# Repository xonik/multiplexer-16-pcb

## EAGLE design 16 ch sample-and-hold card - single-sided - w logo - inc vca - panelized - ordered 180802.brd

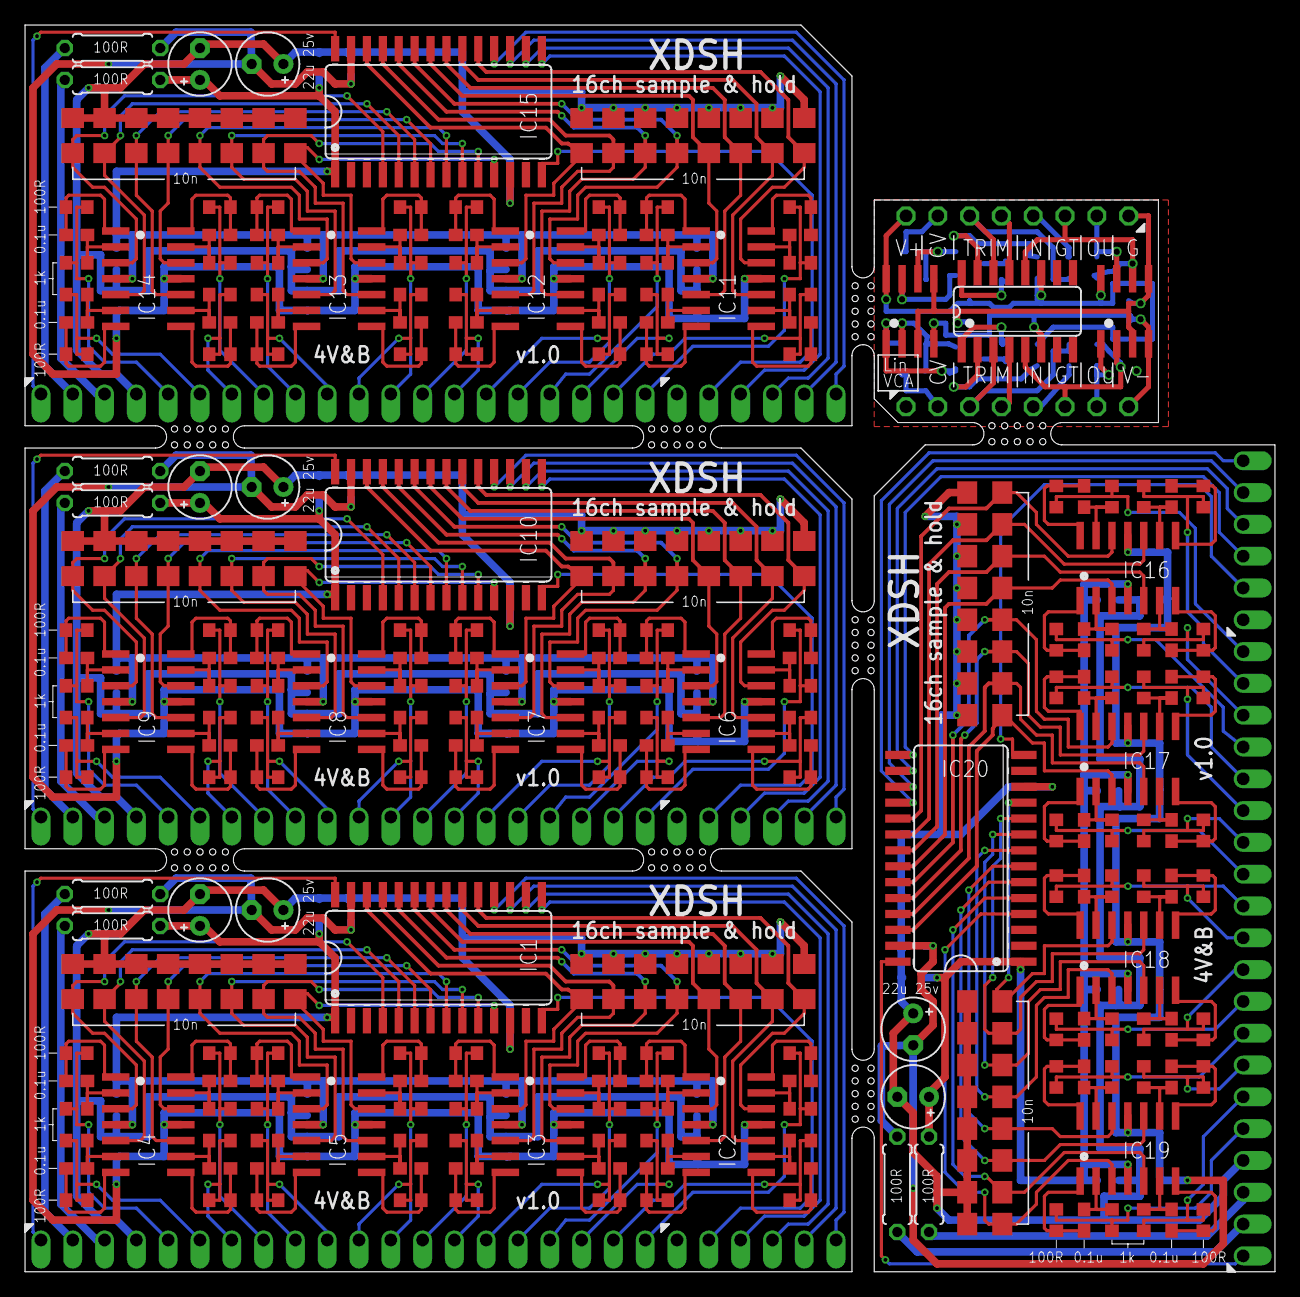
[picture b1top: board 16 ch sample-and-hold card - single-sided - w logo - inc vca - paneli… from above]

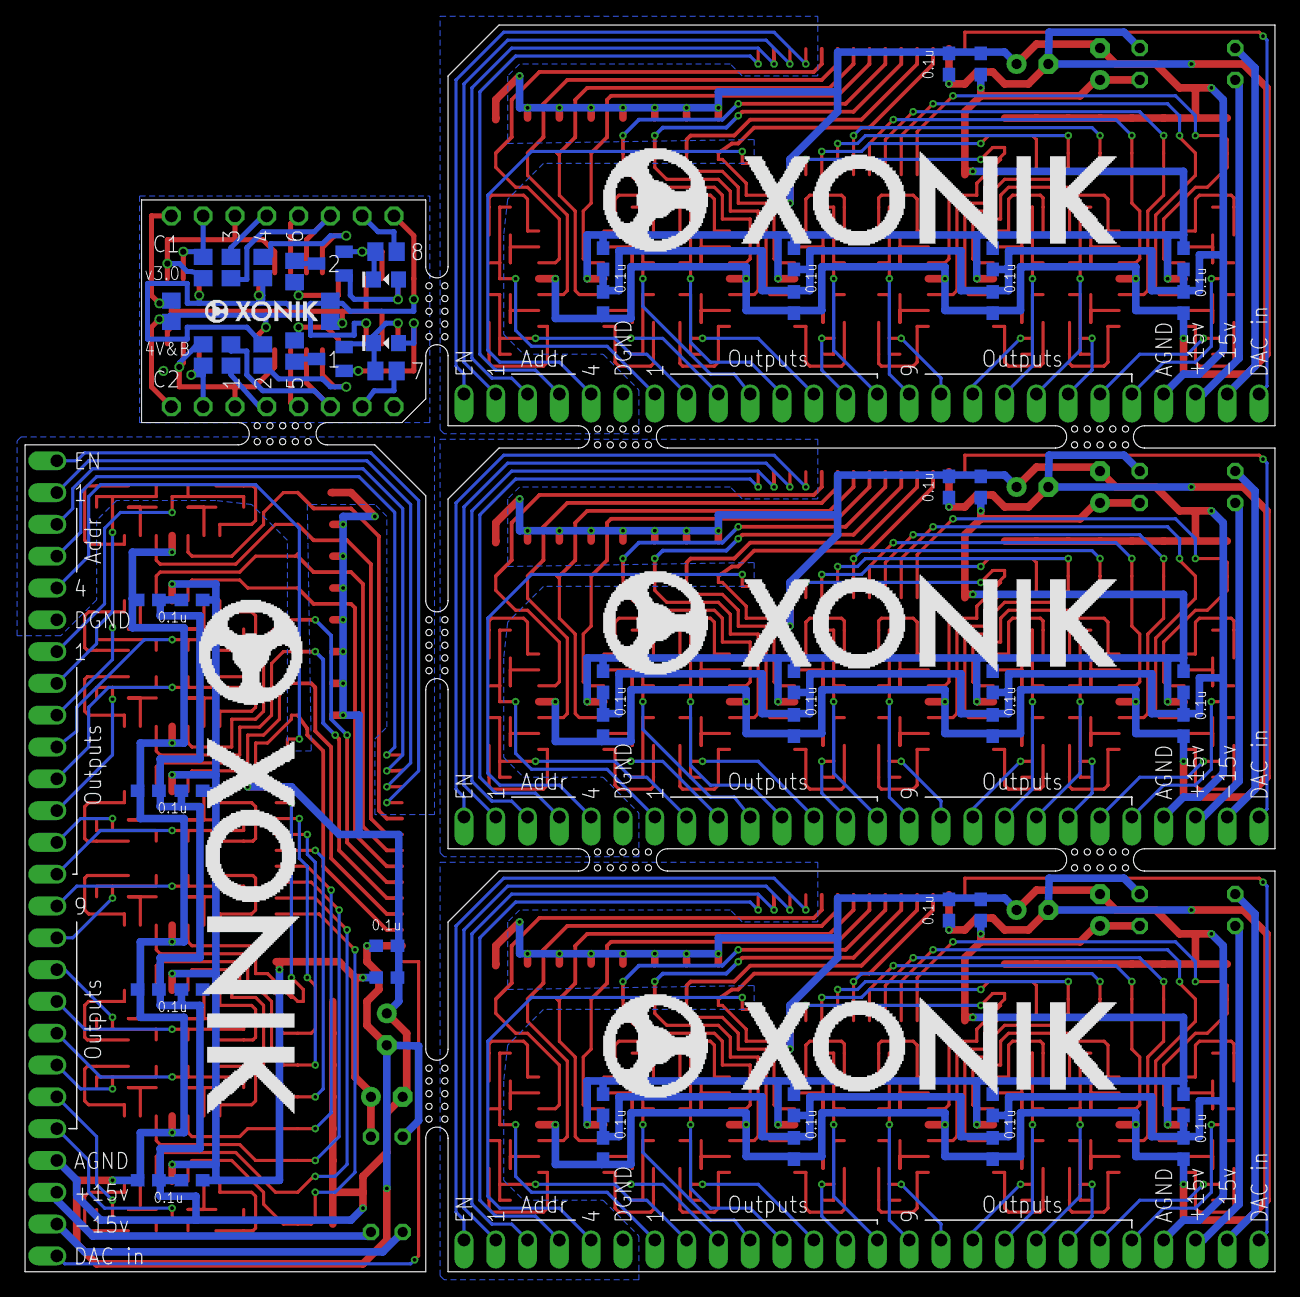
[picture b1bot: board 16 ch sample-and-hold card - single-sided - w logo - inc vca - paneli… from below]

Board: 2 copper layers, 99.8 x 99.6 mm, 361 parts (56 on the bottom side), 325 nets.

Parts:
C1, C12, C13, C14, C15, C16, C17, C18, C19, C20, C21, C30, C31, C32, C33, C34, C35, C36, C37, C38, C39, C40, C41, C42, C43, C44, C48, C49, C51, C52, C53, C58, C59, C60, C61, C62, C67, C68, C69, C70, C71, C76, C77, C78, C79, C80, C81, C84, C85, C86, C87, C88, C92, C93, C95, C96, C97, C102, C103, C104, C105, C106, C111, C112, C113, C114, C115, C120, C121, C122, C123, C124, C125, C128, C129, C130, C131, C132, C136, C137, C139, C140, C141, C146, C147, C148, C149, C150, C155, C156, C157, C158, C159, C164, C165, C166, C167, C168, C169, C172, C173, C174, C175, C176: 0.1uF; C0603
C2, C3, C82, C83, C126, C127, C170, C171: 22uF 25V; E2,5-5
C4, C5, C6, C7, C8, C9, C10, C11, C22, C23, C24, C25, C26, C27, C28, C29, C45, C46, C47, C50, C54, C55, C56, C57, C63, C64, C65, C66, C72, C73, C74, C75, C89, C90, C91, C94, C98, C99, C100, C101, C107, C108, C109, C110, C116, C117, C118, C119, C133, C134, C135, C138, C142, C143, C144, C145, C151, C152, C153, C154, C160, C161, C162, C163: 10nF; C1206
C177, C178: 47p; C0805
C179, C180: 100n; C0805
D1, D2: 1N41480805; D0805-J
IC1, IC10, IC15, IC20: MAX306CWI; SO28L
IC2, IC3, IC4, IC5, IC6, IC7, IC8, IC9, IC11, IC12, IC13, IC14, IC16, IC17, IC18, IC19: TL074D; SO14
IC21: LM13700M; SO16
IC22, IC23: TL072D; SO08
LEFT: MA08-1J
Q1, Q2: MMBT3906LT1SMD; SOT23-BEC
R1, R2, R67, R68, R101, R102, R135, R136: 100R; 0207/7
R3, R5, R7, R9, R11, R13, R15, R17, R19, R21, R23, R25, R27, R29, R31, R33, R36, R38, R40, R41, R44, R46, R48, R49, R52, R54, R56, R57, R60, R62, R64, R65, R70, R72, R74, R75, R78, R80, R82, R83, R86, R88, R90, R91, R94, R96, R98, R99, R104, R106, R108, R109, R112, R114, R116, R117, R120, R122, R124, R125, R128, R130, R132, R133: 1k; R0603
R4, R6, R8, R10, R12, R14, R16, R18, R20, R22, R24, R26, R28, R30, R32, R34, R35, R37, R39, R42, R43, R45, R47, R50, R51, R53, R55, R58, R59, R61, R63, R66, R69, R71, R73, R76, R77, R79, R81, R84, R85, R87, R89, R92, R93, R95, R97, R100, R103, R105, R107, R110, R111, R113, R115, R118, R119, R121, R123, R126, R127, R129, R131, R134: 100R; R0603
R137, R139: 27k; R0805
R138, R140: 12k; R0805
R141, R142: 88k2; R0805
R143, R144: 3k3; R0805
RIGHT: MA08-1J
SV1, SV2, SV3, SV4: SIP-PIN20-1J
U$1, U$2, U$3, U$4: MA06-1JP; SIP-PIN06-1J

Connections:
+15V: C3.+, C12.1, C13.1, C30.1, C31.1, C40.2, IC1.1, IC2.4, IC3.4, IC4.4, IC5.4, R2.1
+15V1: C53.1, C62.1, C71.1, C80.1, C83.+, C84.2, IC6.4, IC7.4, IC8.4, IC9.4, IC10.1, R67.1
+15V2: C97.1, C106.1, C115.1, C124.1, C127.+, C128.2, IC11.4, IC12.4, IC13.4, IC14.4, IC15.1, R101.1
+15V3: C141.1, C150.1, C159.1, C168.1, C171.+, C172.2, IC16.4, IC17.4, IC18.4, IC19.4, IC20.1, R135.1
-15V: C1.1, C2.-, C41.2, C42.2, C43.2, C44.2, IC1.27, IC2.11, IC3.11, IC4.11, IC5.11, R1.1
-15V1: C81.1, C82.-, C85.2, C86.2, C87.2, C88.2, IC6.11, IC7.11, IC8.11, IC9.11, IC10.27, R68.1
-15V2: C125.1, C126.-, C129.2, C130.2, C131.2, C132.2, IC11.11, IC12.11, IC13.11, IC14.11, IC15.27, R102.1
-15V3: C169.1, C170.-, C173.2, C174.2, C175.2, C176.2, IC16.11, IC17.11, IC18.11, IC19.11, IC20.27, R136.1
A0: IC1.17, U$1.5
A1: IC1.16, U$1.4
A2: IC1.15, U$1.3
A3: IC1.14, U$1.2
A4: IC10.14, U$2.2
A5: IC10.17, U$2.5
A6: IC10.16, U$2.4
A7: IC10.15, U$2.3
A8: IC15.14, U$3.2
A9: IC15.17, U$3.5
A10: IC15.16, U$3.4
A11: IC15.15, U$3.3
A12: IC20.14, U$4.2
A13: IC20.17, U$4.5
A14: IC20.16, U$4.4
A15: IC20.15, U$4.3
AGND: C1.2, C2.+, C3.-, C4.1, C5.1, C6.1, C7.1, C8.1, C9.1, C10.1, C11.1, C12.2, C13.2, C22.1, C23.1, C24.1, C25.1, C26.1, C27.1, C28.1, C29.1, C30.2, C31.2, C40.1, C41.1, C42.1, C43.1, C44.1, IC1.12, SV1.4
AGND1: C45.1, C46.1, C47.1, C50.1, C53.2, C54.1, C55.1, C56.1, C57.1, C62.2, C63.1, C64.1, C65.1, C66.1, C71.2, C72.1, C73.1, C74.1, C75.1, C80.2, C81.2, C82.+, C83.-, C84.1, C85.1, C86.1, C87.1, C88.1, IC10.12, SV2.4
AGND2: C89.1, C90.1, C91.1, C94.1, C97.2, C98.1, C99.1, C100.1, C101.1, C106.2, C107.1, C108.1, C109.1, C110.1, C115.2, C116.1, C117.1, C118.1, C119.1, C124.2, C125.2, C126.+, C127.-, C128.1, C129.1, C130.1, C131.1, C132.1, IC15.12, SV3.4
AGND3: C133.1, C134.1, C135.1, C138.1, C141.2, C142.1, C143.1, C144.1, C145.1, C150.2, C151.1, C152.1, C153.1, C154.1, C159.2, C160.1, C161.1, C162.1, C163.1, C168.2, C169.2, C170.+, C171.-, C172.1, C173.1, C174.1, C175.1, C176.1, IC20.12, SV4.4
CV1: LEFT.2, R143.2
CV2: R144.2, RIGHT.7
DAC: IC1.28, SV1.1
DAC1: IC10.28, SV2.1
DAC2: IC15.28, SV3.1
DAC3: IC20.28, SV4.1
EN: IC1.18, U$1.6
EN1: IC10.18, U$2.6
EN2: IC15.18, U$3.6
EN3: IC20.18, U$4.6
GAIN_TRIM1: C178.1, IC21.5, IC23.2, LEFT.6
GAIN_TRIM2: C177.1, IC21.12, IC23.6, RIGHT.3
GND: C179.1, C180.2, IC22.3, IC22.5, IC23.3, IC23.5, RIGHT.1
IN1: C4.2, IC1.19, IC2.12
IN2: C50.2, IC6.12, IC10.19
IN3: C5.2, IC1.20, IC2.10
IN4: C6.2, IC1.21, IC2.5
IN5: C47.2, IC6.10, IC10.20
IN6: C7.2, IC1.22, IC2.3
IN7: C46.2, IC6.5, IC10.21
IN8: C45.2, IC6.3, IC10.22
IN9: C8.2, IC1.23, IC3.12
IN10: C57.2, IC7.12, IC10.23
IN11: C9.2, IC1.24, IC3.10
IN12: C10.2, IC1.25, IC3.5
IN13: C56.2, IC7.10, IC10.24
IN14: C11.2, IC1.26, IC3.3
IN15: C55.2, IC7.5, IC10.25
IN16: C54.2, IC7.3, IC10.26
IN17: C26.2, IC1.11, IC5.12
IN18: C63.2, IC8.3, IC10.8
IN19: C27.2, IC1.10, IC5.10
IN20: C28.2, IC1.9, IC5.5
IN21: C64.2, IC8.5, IC10.9
IN22: C29.2, IC1.8, IC5.3
IN23: C65.2, IC8.10, IC10.10
IN24: C66.2, IC8.12, IC10.11
IN25: C22.2, IC1.7, IC4.12
IN26: C72.2, IC9.3, IC10.4
IN27: C23.2, IC1.6, IC4.10
IN28: C24.2, IC1.5, IC4.5
IN29: C73.2, IC9.5, IC10.5
IN30: C25.2, IC1.4, IC4.3
IN31: C74.2, IC9.10, IC10.6
IN32: C75.2, IC9.12, IC10.7
IN33: C94.2, IC11.12, IC15.19
IN34: C91.2, IC11.10, IC15.20
IN35: C90.2, IC11.5, IC15.21
IN36: C89.2, IC11.3, IC15.22
IN37: C101.2, IC12.12, IC15.23
IN38: C100.2, IC12.10, IC15.24
IN39: C99.2, IC12.5, IC15.25
IN40: C98.2, IC12.3, IC15.26
IN41: C107.2, IC13.3, IC15.8
IN42: C108.2, IC13.5, IC15.9
IN43: C109.2, IC13.10, IC15.10
IN44: C110.2, IC13.12, IC15.11
IN45: C116.2, IC14.3, IC15.4
IN46: C117.2, IC14.5, IC15.5
IN47: C118.2, IC14.10, IC15.6
IN48: C119.2, IC14.12, IC15.7
IN49: C138.2, IC16.12, IC20.19
IN50: C135.2, IC16.10, IC20.20
IN51: C134.2, IC16.5, IC20.21
IN52: C133.2, IC16.3, IC20.22
IN53: C145.2, IC17.12, IC20.23
IN54: C144.2, IC17.10, IC20.24
IN55: C143.2, IC17.5, IC20.25
IN56: C142.2, IC17.3, IC20.26
IN57: C151.2, IC18.3, IC20.8
IN58: C152.2, IC18.5, IC20.9
IN59: C153.2, IC18.10, IC20.10
IN60: C154.2, IC18.12, IC20.11
IN61: C160.2, IC19.3, IC20.4
IN62: C161.2, IC19.5, IC20.5
IN63: C162.2, IC19.10, IC20.6
IN64: C163.2, IC19.12, IC20.7
IN65: LEFT.5, R137.1
IN66: R139.1, RIGHT.4
unnamed: C17.2, IC2.2, R9.1
unnamed: C17.1, IC2.1, R10.1
unnamed: C16.1, IC2.7, R8.1
unnamed: C15.1, IC2.8, R6.1
unnamed: C16.2, IC2.6, R7.1
unnamed: C14.1, IC2.14, R4.1
unnamed: C15.2, IC2.9, R5.1
unnamed: C14.2, IC2.13, R3.1
unnamed: C21.1, IC3.1, R18.1
unnamed: C21.2, IC3.2, R17.1
unnamed: C48.1, IC6.1, R35.1
unnamed: C48.2, IC6.2, R36.1
unnamed: C49.1, IC6.7, R37.1
unnamed: C49.2, IC6.6, R38.1
unnamed: C51.1, IC6.8, R39.1
unnamed: C52.1, IC6.14, R42.1
unnamed: C51.2, IC6.9, R40.1
unnamed: C52.2, IC6.13, R41.1
unnamed: C20.1, IC3.7, R16.1
unnamed: C20.2, IC3.6, R15.1
unnamed: C19.1, IC3.8, R14.1
unnamed: C18.1, IC3.14, R12.1
unnamed: C19.2, IC3.9, R13.1
unnamed: C18.2, IC3.13, R11.1
unnamed: C58.1, IC7.1, R43.1
unnamed: C58.2, IC7.2, R44.1
unnamed: C59.1, IC7.7, R45.1
unnamed: C59.2, IC7.6, R46.1
unnamed: C60.1, IC7.8, R47.1
unnamed: C61.1, IC7.14, R50.1
unnamed: C60.2, IC7.9, R48.1
unnamed: C61.2, IC7.13, R49.1
unnamed: C39.1, IC5.1, R34.1
unnamed: C39.2, IC5.2, R33.1
unnamed: C38.1, IC5.7, R32.1
unnamed: C38.2, IC5.6, R31.1
unnamed: C37.1, IC5.8, R30.1
unnamed: C36.1, IC5.14, R28.1
unnamed: C37.2, IC5.9, R29.1
unnamed: C36.2, IC5.13, R27.1
unnamed: C67.1, IC8.1, R51.1
unnamed: C67.2, IC8.2, R52.1
unnamed: C68.1, IC8.7, R53.1
unnamed: C68.2, IC8.6, R54.1
unnamed: C69.1, IC8.8, R55.1
unnamed: C70.1, IC8.14, R58.1
unnamed: C69.2, IC8.9, R56.1
unnamed: C70.2, IC8.13, R57.1
unnamed: C35.1, IC4.1, R26.1
unnamed: C35.2, IC4.2, R25.1
unnamed: C34.1, IC4.7, R24.1
unnamed: C34.2, IC4.6, R23.1
unnamed: C33.1, IC4.8, R22.1
unnamed: C32.1, IC4.14, R20.1
unnamed: C33.2, IC4.9, R21.1
unnamed: C32.2, IC4.13, R19.1
unnamed: C76.1, IC9.1, R59.1
unnamed: C76.2, IC9.2, R60.1
unnamed: C77.1, IC9.7, R61.1
unnamed: C77.2, IC9.6, R62.1
unnamed: C78.1, IC9.8, R63.1
unnamed: C79.1, IC9.14, R66.1
unnamed: C78.2, IC9.9, R64.1
unnamed: C79.2, IC9.13, R65.1
unnamed: C92.1, IC11.1, R69.1
unnamed: C92.2, IC11.2, R70.1
unnamed: C93.1, IC11.7, R71.1
unnamed: C93.2, IC11.6, R72.1
unnamed: C95.1, IC11.8, R73.1
unnamed: C96.1, IC11.14, R76.1
unnamed: C95.2, IC11.9, R74.1
unnamed: C96.2, IC11.13, R75.1
unnamed: C102.1, IC12.1, R77.1
unnamed: C102.2, IC12.2, R78.1
unnamed: C103.1, IC12.7, R79.1
unnamed: C103.2, IC12.6, R80.1
unnamed: C104.1, IC12.8, R81.1
unnamed: C105.1, IC12.14, R84.1
unnamed: C104.2, IC12.9, R82.1
unnamed: C105.2, IC12.13, R83.1
unnamed: C111.1, IC13.1, R85.1
unnamed: C111.2, IC13.2, R86.1
unnamed: C112.1, IC13.7, R87.1
unnamed: C112.2, IC13.6, R88.1
unnamed: C113.1, IC13.8, R89.1
unnamed: C114.1, IC13.14, R92.1
unnamed: C113.2, IC13.9, R90.1
unnamed: C114.2, IC13.13, R91.1
unnamed: C120.1, IC14.1, R93.1
unnamed: C120.2, IC14.2, R94.1
unnamed: C121.1, IC14.7, R95.1
unnamed: C121.2, IC14.6, R96.1
unnamed: C122.1, IC14.8, R97.1
unnamed: C123.1, IC14.14, R100.1
unnamed: C122.2, IC14.9, R98.1
unnamed: C123.2, IC14.13, R99.1
unnamed: C136.1, IC16.1, R103.1
unnamed: C136.2, IC16.2, R104.1
unnamed: C137.1, IC16.7, R105.1
unnamed: C137.2, IC16.6, R106.1
unnamed: C139.1, IC16.8, R107.1
unnamed: C140.1, IC16.14, R110.1
unnamed: C139.2, IC16.9, R108.1
unnamed: C140.2, IC16.13, R109.1
unnamed: C146.1, IC17.1, R111.1
unnamed: C146.2, IC17.2, R112.1
unnamed: C147.1, IC17.7, R113.1
unnamed: C147.2, IC17.6, R114.1
unnamed: C148.1, IC17.8, R115.1
unnamed: C149.1, IC17.14, R118.1
unnamed: C148.2, IC17.9, R116.1
unnamed: C149.2, IC17.13, R117.1
unnamed: C155.1, IC18.1, R119.1
unnamed: C155.2, IC18.2, R120.1
unnamed: C156.1, IC18.7, R121.1
unnamed: C156.2, IC18.6, R122.1
unnamed: C157.1, IC18.8, R123.1
unnamed: C158.1, IC18.14, R126.1
unnamed: C157.2, IC18.9, R124.1
unnamed: C158.2, IC18.13, R125.1
unnamed: C164.1, IC19.1, R127.1
unnamed: C164.2, IC19.2, R128.1
unnamed: C165.1, IC19.7, R129.1
unnamed: C165.2, IC19.6, R130.1
unnamed: C166.1, IC19.8, R131.1
unnamed: C167.1, IC19.14, R134.1
unnamed: C166.2, IC19.9, R132.1
unnamed: C167.2, IC19.13, R133.1
unnamed: Q1.C, R141.1
unnamed: Q2.C, R142.1
unnamed: D1.C, IC22.2, Q1.E, R143.1
unnamed: IC21.1, R141.2
unnamed: IC21.2, R138.2
unnamed: IC21.16, R142.2
unnamed: D2.C, IC22.6, Q2.E, R144.1
unnamed: IC21.15, R140.2
unnamed: D2.A, IC22.7, Q2.B
unnamed: D1.A, IC22.1, Q1.B
OUT0: R3.2, R4.2, SV1.20
OUT1: R5.2, R6.2, SV1.19
OUT2: R41.2, R42.2, SV2.20
OUT3: R37.2, R38.2, SV2.18
OUT4: R35.2, R36.2, SV2.17
OUT5: R39.2, R40.2, SV2.19
OUT6: R7.2, R8.2, SV1.18
OUT7: R9.2, R10.2, SV1.17
OUT8: R11.2, R12.2, SV1.16
OUT9: R13.2, R14.2, SV1.15
OUT10: R43.2, R44.2, SV2.13
OUT11: R45.2, R46.2, SV2.14
OUT12: R47.2, R48.2, SV2.15
OUT13: R49.2, R50.2, SV2.16
OUT14: R15.2, R16.2, SV1.14
OUT15: R17.2, R18.2, SV1.13
OUT16: R27.2, R28.2, SV1.12
OUT17: R29.2, R30.2, SV1.11
OUT18: R51.2, R52.2, SV2.9
OUT19: R53.2, R54.2, SV2.10
OUT20: R55.2, R56.2, SV2.11
OUT21: R57.2, R58.2, SV2.12
OUT22: R31.2, R32.2, SV1.10
OUT23: R33.2, R34.2, SV1.9
OUT24: R19.2, R20.2, SV1.8
OUT25: R21.2, R22.2, SV1.7
OUT26: R59.2, R60.2, SV2.5
OUT27: R61.2, R62.2, SV2.6
OUT28: R63.2, R64.2, SV2.7
OUT29: R65.2, R66.2, SV2.8
OUT30: R23.2, R24.2, SV1.6
OUT31: R25.2, R26.2, SV1.5
OUT32: R75.2, R76.2, SV3.20
OUT33: R71.2, R72.2, SV3.18
OUT34: R69.2, R70.2, SV3.17
OUT35: R73.2, R74.2, SV3.19
OUT36: R77.2, R78.2, SV3.13
OUT37: R79.2, R80.2, SV3.14
OUT38: R81.2, R82.2, SV3.15
OUT39: R83.2, R84.2, SV3.16
OUT40: R85.2, R86.2, SV3.9
OUT41: R87.2, R88.2, SV3.10
OUT42: R89.2, R90.2, SV3.11
OUT43: R91.2, R92.2, SV3.12
OUT44: R93.2, R94.2, SV3.5
OUT45: R95.2, R96.2, SV3.6
OUT46: R97.2, R98.2, SV3.7
OUT47: R99.2, R100.2, SV3.8
OUT48: R109.2, R110.2, SV4.20
OUT49: R105.2, R106.2, SV4.18
OUT50: R103.2, R104.2, SV4.17
OUT51: R107.2, R108.2, SV4.19
OUT52: R111.2, R112.2, SV4.13
OUT53: R113.2, R114.2, SV4.14
OUT54: R115.2, R116.2, SV4.15
OUT55: R117.2, R118.2, SV4.16
OUT56: R119.2, R120.2, SV4.9
OUT57: R121.2, R122.2, SV4.10
OUT58: R123.2, R124.2, SV4.11
OUT59: R125.2, R126.2, SV4.12
OUT60: R127.2, R128.2, SV4.5
OUT61: R129.2, R130.2, SV4.6
OUT62: R131.2, R132.2, SV4.7
OUT63: R133.2, R134.2, SV4.8
OUT64: C178.2, IC23.1, LEFT.7
OUT65: C177.2, IC23.7, RIGHT.2
TRIM1+: IC21.3, LEFT.3, R137.2
TRIM1-: IC21.4, LEFT.4
TRIM2+: IC21.14, R139.2, RIGHT.6
TRIM2-: IC21.13, RIGHT.5
V+: R2.2, SV1.3
V+1: R67.2, SV2.3
V+2: R101.2, SV3.3
V+3: R135.2, SV4.3
V+4: C179.2, IC21.11, IC22.8, IC23.8, R138.1, R140.1, RIGHT.8
V-: R1.2, SV1.2
V-1: R68.2, SV2.2
V-2: R102.2, SV3.2
V-3: R136.2, SV4.2
V-4: C180.1, IC21.6, IC22.4, IC23.4, LEFT.8

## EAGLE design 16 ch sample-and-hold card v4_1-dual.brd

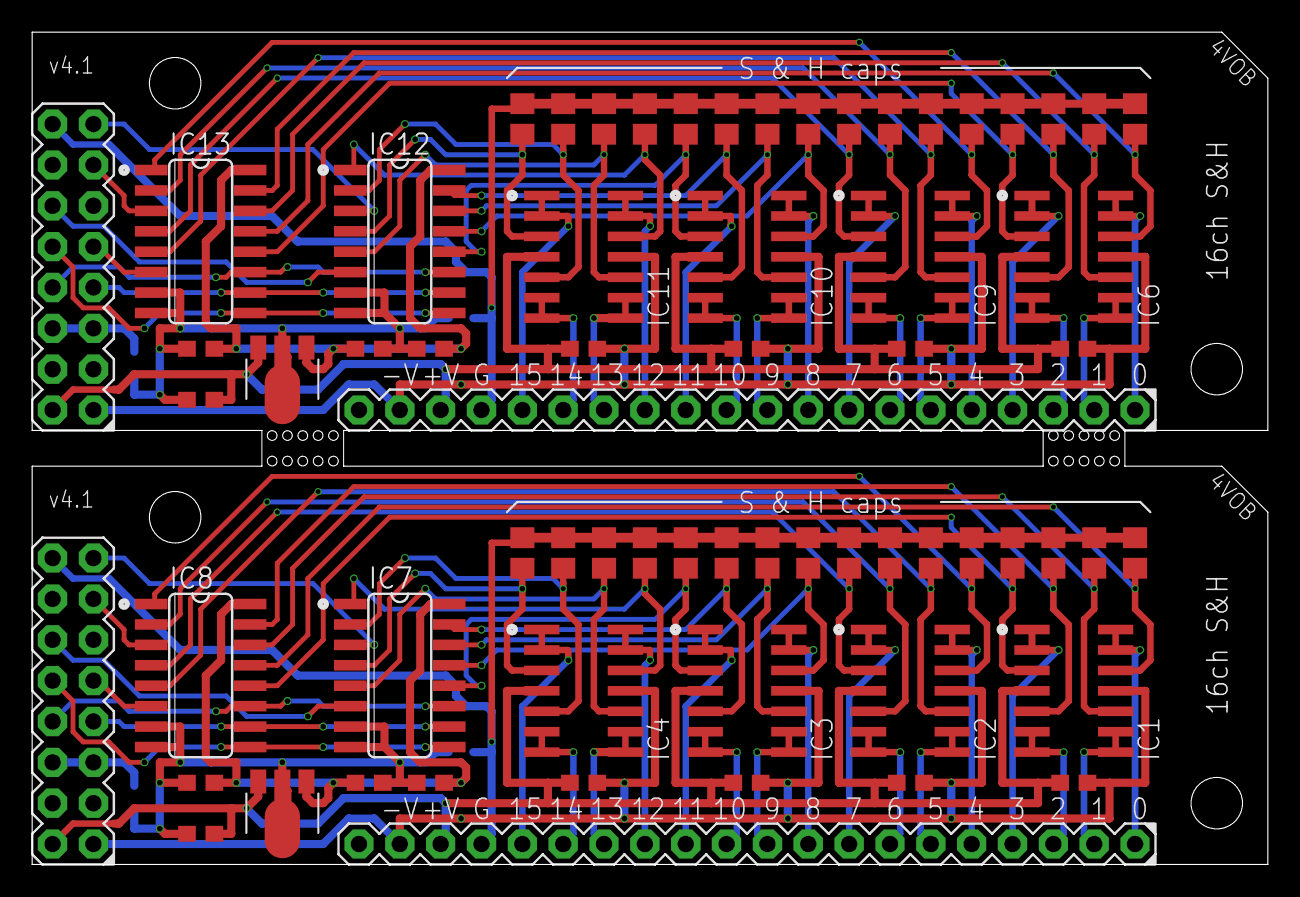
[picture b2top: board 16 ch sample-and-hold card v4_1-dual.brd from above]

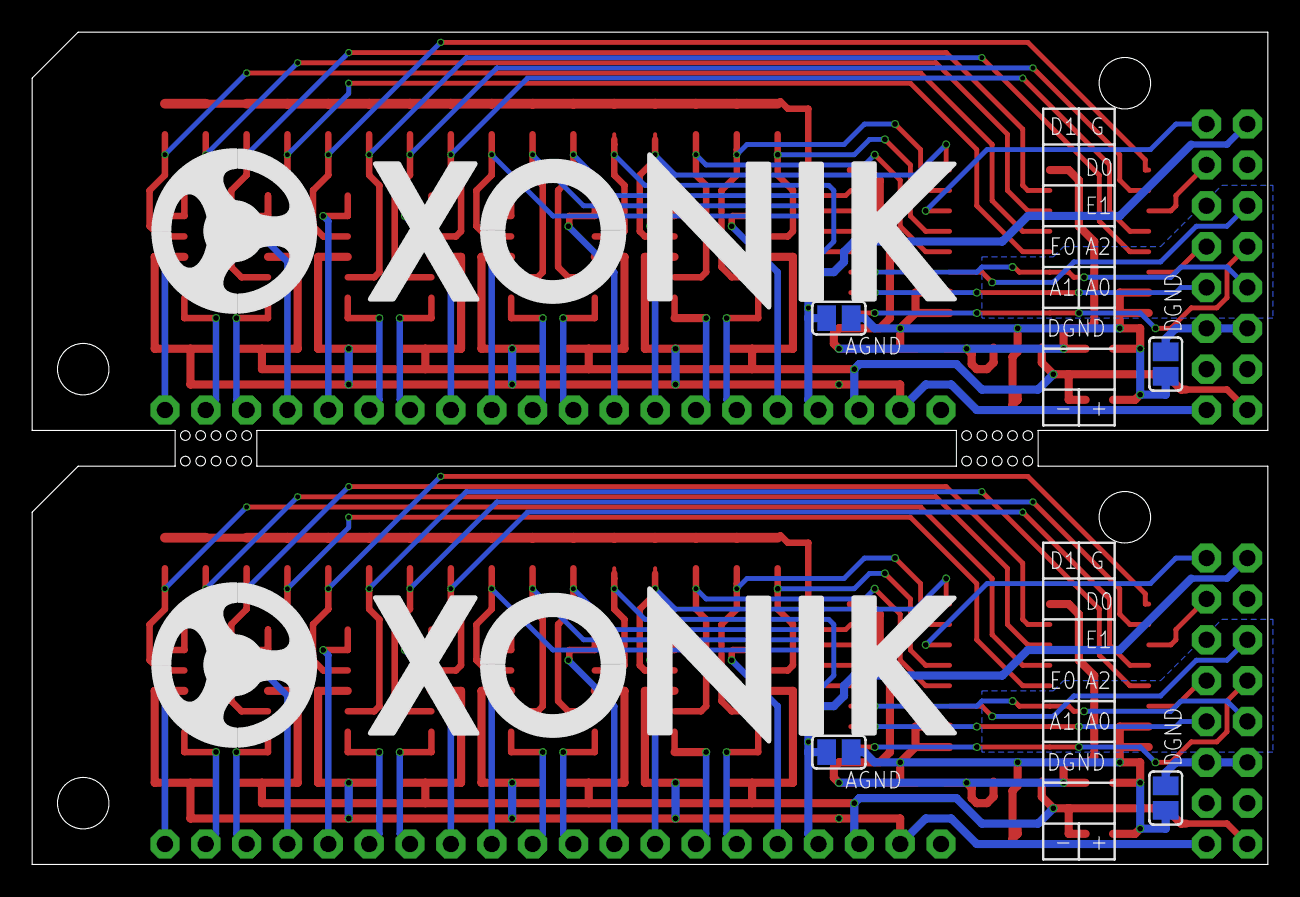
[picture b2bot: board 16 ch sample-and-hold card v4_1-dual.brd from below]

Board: 2 copper layers, 76.8 x 51.8 mm, 72 parts (6 on the bottom side), 90 nets.

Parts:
C1, C2, C12, C13, C18, C30, C31, C33, C38, C40, C44, C45, C46, C47: 0.1uF; C0603
C3, C48: 0.33uF; C0603
C4, C5, C6, C7, C8, C9, C10, C11, C14, C15, C16, C17, C19, C20, C21, C22, C23, C24, C25, C26, C27, C28, C29, C32, C34, C35, C36, C37, C39, C41, C42, C43: 10nF; C0805
IC1, IC2, IC3, IC4, IC6, IC9, IC10, IC11: TL074D; SO14
IC5, IC14: 78L05F; SOT89
IC7, IC8, IC12, IC13: 4051D; SO16
SJ1, SJ2, SJ3, SJ4: SJ
SV1, SV2: MA20-1
SV3, SV4: MA08-2J
U$1, U$2: XONIK_LOGO_50

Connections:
+5V: C1.2, C2.2, C40.2, IC5.1, IC7.16, IC8.16
+5V1: C45.2, C46.2, C47.2, IC12.16, IC13.16, IC14.1
+15V: C3.2, C12.1, C13.1, C30.1, C31.1, IC1.4, IC2.4, IC3.4, IC4.4, IC5.3, SV2.18, SV3.2
+15V1: C18.1, C33.1, C38.1, C44.1, C48.2, IC6.4, IC9.4, IC10.4, IC11.4, IC14.3, SV1.18, SV4.2
-15V: C12.2, C13.2, C30.2, C31.2, IC1.11, IC2.11, IC3.11, IC4.11, SV2.19, SV3.1
-15V1: C18.2, C33.2, C38.2, C44.2, IC6.11, IC9.11, IC10.11, IC11.11, SV1.19, SV4.1
A0: IC7.11, IC8.11, SV3.8
A1: IC7.10, IC8.10, SV3.7
A2: IC7.9, IC8.9, SV3.10
A3: IC12.11, IC13.11, SV4.8
A4: IC12.10, IC13.10, SV4.7
A5: IC12.9, IC13.9, SV4.10
AGND: C4.1, C5.1, C6.1, C7.1, C8.1, C9.1, C10.1, C11.1, C22.1, C23.1, C24.1, C25.1, C26.1, C27.1, C28.1, C29.1, SJ1.2, SV2.17, SV3.16
AGND1: C14.1, C15.1, C16.1, C17.1, C19.1, C20.1, C21.1, C32.1, C34.1, C35.1, C36.1, C37.1, C39.1, C41.1, C42.1, C43.1, SJ3.2, SV1.17, SV4.16
DAC0: IC8.3, SV3.13
DAC1: IC7.3, SV3.15
DAC2: IC12.3, SV4.15
DAC3: IC13.3, SV4.13
DGND: SJ2.1, SV3.5, SV3.6
DGND1: SJ4.1, SV4.5, SV4.6
EN0: IC8.6, SV3.9
EN1: IC7.6, SV3.12
EN2: IC13.6, SV4.9
EN3: IC12.6, SV4.12
IN_0: C4.2, IC1.12, IC8.13
IN_1: C5.2, IC1.10, IC8.14
IN_2: C6.2, IC1.5, IC8.15
IN_3: C7.2, IC1.3, IC8.12
IN_4: C8.2, IC2.12, IC8.1
IN_5: C9.2, IC2.10, IC8.5
IN_6: C10.2, IC2.5, IC8.2
IN_7: C11.2, IC2.3, IC8.4
IN_8: C26.2, IC3.12, IC7.13
IN_9: C27.2, IC3.10, IC7.14
IN_10: C28.2, IC3.5, IC7.15
IN_11: C29.2, IC3.3, IC7.12
IN_12: C22.2, IC4.12, IC7.1
IN_13: C23.2, IC4.10, IC7.5
IN_14: C24.2, IC4.5, IC7.2
IN_15: C25.2, IC4.3, IC7.4
IN_16: C17.2, IC6.12, IC13.13
IN_17: C16.2, IC6.10, IC13.14
IN_18: C15.2, IC6.5, IC13.15
IN_19: C14.2, IC6.3, IC13.12
IN_20: C32.2, IC9.12, IC13.1
IN_21: C21.2, IC9.10, IC13.5
IN_22: C20.2, IC9.5, IC13.2
IN_23: C19.2, IC9.3, IC13.4
IN_24: C34.2, IC10.3, IC12.12
IN_25: C35.2, IC10.5, IC12.15
IN_26: C36.2, IC10.10, IC12.14
IN_27: C37.2, IC10.12, IC12.13
IN_28: C39.2, IC11.3, IC12.4
IN_29: C41.2, IC11.5, IC12.2
IN_30: C42.2, IC11.10, IC12.5
IN_31: C43.2, IC11.12, IC12.1
unnamed: C45.1, C46.1, C47.1, C48.1, IC12.7, IC12.8, IC13.7, IC13.8, IC14.2, IC14.2@1, SJ3.1, SJ4.2
unnamed: C1.1, C2.1, C3.1, C40.1, IC5.2, IC5.2@1, IC7.7, IC7.8, IC8.7, IC8.8, SJ1.1, SJ2.2
OUT_0: IC1.13, IC1.14, SV2.1
OUT_1: IC1.8, IC1.9, SV2.2
OUT_2: IC1.6, IC1.7, SV2.3
OUT_3: IC1.1, IC1.2, SV2.4
OUT_4: IC2.13, IC2.14, SV2.5
OUT_5: IC2.8, IC2.9, SV2.6
OUT_6: IC2.6, IC2.7, SV2.7
OUT_7: IC2.1, IC2.2, SV2.8
OUT_8: IC3.13, IC3.14, SV2.9
OUT_9: IC3.8, IC3.9, SV2.10
OUT_10: IC3.6, IC3.7, SV2.11
OUT_11: IC3.1, IC3.2, SV2.12
OUT_12: IC4.13, IC4.14, SV2.13
OUT_13: IC4.8, IC4.9, SV2.14
OUT_14: IC4.6, IC4.7, SV2.15
OUT_15: IC4.1, IC4.2, SV2.16
OUT_16: IC6.13, IC6.14, SV1.1
OUT_17: IC6.6, IC6.7, SV1.3
OUT_18: IC6.1, IC6.2, SV1.4
OUT_19: IC6.8, IC6.9, SV1.2
OUT_20: IC9.1, IC9.2, SV1.8
OUT_21: IC9.6, IC9.7, SV1.7
OUT_22: IC9.8, IC9.9, SV1.6
OUT_23: IC9.13, IC9.14, SV1.5
OUT_24: IC10.1, IC10.2, SV1.12
OUT_25: IC10.6, IC10.7, SV1.11
OUT_26: IC10.8, IC10.9, SV1.10
OUT_27: IC10.13, IC10.14, SV1.9
OUT_28: IC11.6, IC11.7, SV1.15
OUT_29: IC11.8, IC11.9, SV1.14
OUT_30: IC11.13, IC11.14, SV1.13
OUT_31: IC11.1, IC11.2, SV1.16

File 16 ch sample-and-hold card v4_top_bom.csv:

Comment,Designator,Footprint,LCSC Part #
0.1uF,C1 C2 C12 C13 C30 C31 C40,C0603,
0.33uF,C3,C0603,
10nF,C4 C5 C6 C7 C8 C9 C10 C11 C22 C23 C24 C25 C26 C27 C28 C29,C1206,
78L05F,IC5,SOT89,
4051D,IC7 IC8,SO16,

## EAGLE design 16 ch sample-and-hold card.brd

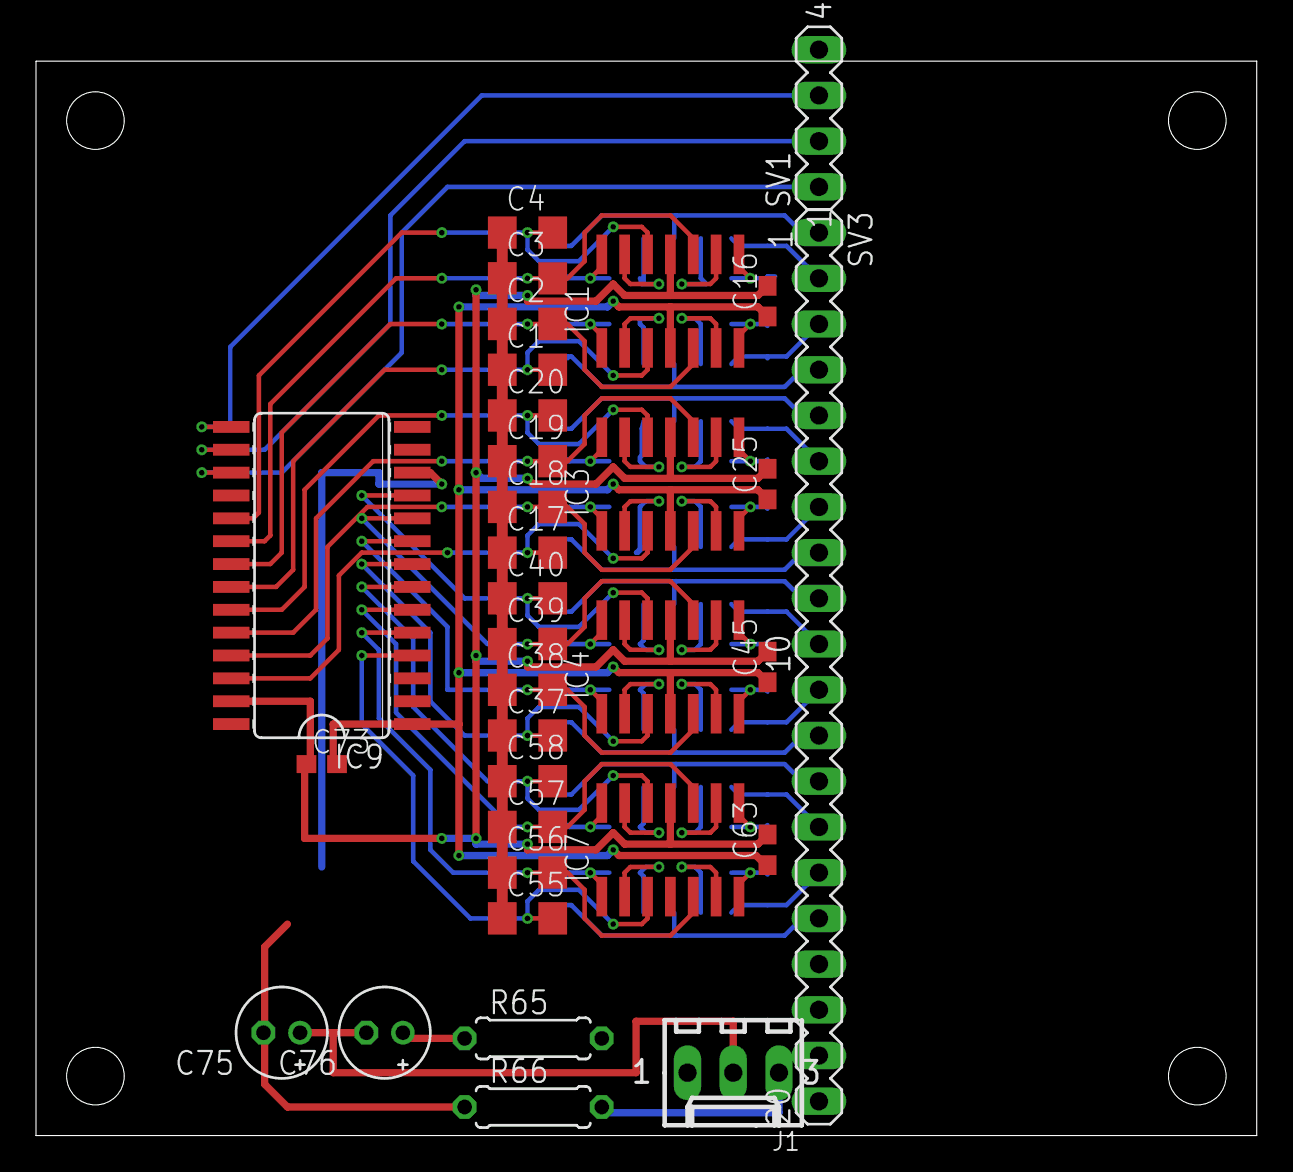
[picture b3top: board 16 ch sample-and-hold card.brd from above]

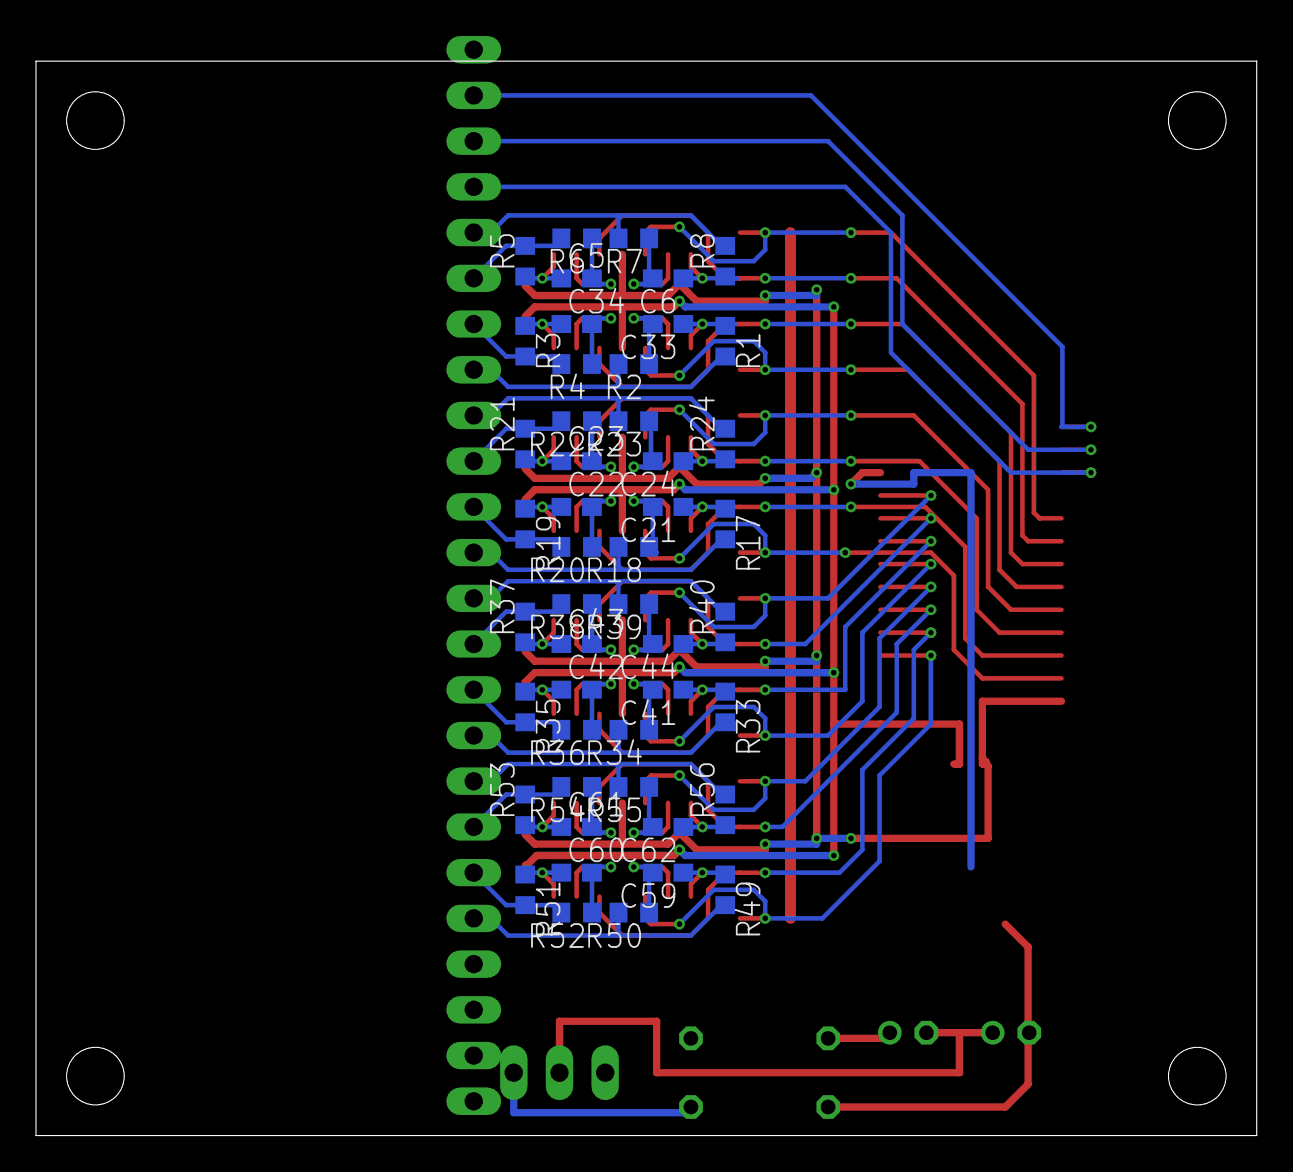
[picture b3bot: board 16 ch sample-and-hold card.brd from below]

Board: 2 copper layers, 67.8 x 59.7 mm, 81 parts (48 on the bottom side), 74 nets.

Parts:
C1, C2, C3, C4, C17, C18, C19, C20, C37, C38, C39, C40, C55, C56, C57, C58: C1206
C5, C6, C16, C21, C22, C23, C24, C25, C33, C34, C41, C42, C43, C44, C45, C59, C60, C61, C62, C63, C73: 0.1uF; C0603
C75, C76: 22uF 25V; E2-5
IC1, IC3, IC4, IC7: TL074D; SO14
IC9: MAX306CWI; SO28L
J1: 22-27-2031-03; 6410-03
R1, R3, R5, R8, R17, R19, R21, R24, R33, R35, R37, R40, R49, R51, R53, R56: 100R; R0603
R2, R4, R6, R7, R18, R20, R22, R23, R34, R36, R38, R39, R50, R52, R54, R55: 1k; R0603
R65, R66: 100; 0207/7
SV1: MA04-1
SV3: MA20-1

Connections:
+15V: C16.1, C25.1, C45.1, C63.1, C73.2, C76.+, IC1.4, IC3.4, IC4.4, IC7.4, IC9.1, R65.1
-15V: C16.2, C25.2, C45.2, C63.2, C73.1, C75.-, IC1.11, IC3.11, IC4.11, IC7.11, IC9.27, R66.1
A0: IC9.17, SV1.1
A1: IC9.16, SV1.2
A2: IC9.15, SV1.3
A3: IC9.14, SV1.4
AGND: C1.1, C2.1, C3.1, C4.1, C17.1, C18.1, C19.1, C20.1, C37.1, C38.1, C39.1, C40.1, C55.1, C56.1, C57.1, C58.1, C75.+, C76.-, IC9.12, J1.2, SV3.18
EN0: IC9.18, SV3.20
IN1: C4.2, IC1.12, IC9.19
IN3: C3.2, IC1.10, IC9.20
IN4: C2.2, IC1.5, IC9.21
IN6: C1.2, IC1.3, IC9.22
IN9: C20.2, IC3.12, IC9.23
IN11: C19.2, IC3.10, IC9.24
IN12: C18.2, IC3.5, IC9.25
IN14: C17.2, IC3.3, IC9.26
IN17: C40.2, IC4.12, IC9.11
IN19: C39.2, IC4.10, IC9.10
IN20: C38.2, IC4.5, IC9.9
IN22: C37.2, IC4.3, IC9.8
IN25: C58.2, IC7.12, IC9.7
IN27: C57.2, IC7.10, IC9.6
IN28: C56.2, IC7.5, IC9.5
IN30: C55.2, IC7.3, IC9.4
unnamed: C33.2, IC1.2, R2.1
unnamed: C33.1, IC1.1, R1.1
unnamed: C34.1, IC1.7, R3.1
unnamed: C5.1, IC1.8, R5.1
unnamed: C34.2, IC1.6, R4.1
unnamed: C6.1, IC1.14, R8.1
unnamed: C5.2, IC1.9, R6.1
unnamed: C6.2, IC1.13, R7.1
unnamed: C21.1, IC3.1, R17.1
unnamed: C21.2, IC3.2, R18.1
unnamed: C22.1, IC3.7, R19.1
unnamed: C22.2, IC3.6, R20.1
unnamed: C23.1, IC3.8, R21.1
unnamed: C24.1, IC3.14, R24.1
unnamed: C23.2, IC3.9, R22.1
unnamed: C24.2, IC3.13, R23.1
unnamed: C41.1, IC4.1, R33.1
unnamed: C41.2, IC4.2, R34.1
unnamed: C42.1, IC4.7, R35.1
unnamed: C42.2, IC4.6, R36.1
unnamed: C43.1, IC4.8, R37.1
unnamed: C44.1, IC4.14, R40.1
unnamed: C43.2, IC4.9, R38.1
unnamed: C44.2, IC4.13, R39.1
unnamed: C59.1, IC7.1, R49.1
unnamed: C59.2, IC7.2, R50.1
unnamed: C60.1, IC7.7, R51.1
unnamed: C60.2, IC7.6, R52.1
unnamed: C61.1, IC7.8, R53.1
unnamed: C62.1, IC7.14, R56.1
unnamed: C61.2, IC7.9, R54.1
unnamed: C62.2, IC7.13, R55.1
OUT0: R7.2, R8.2, SV3.1
OUT1: R5.2, R6.2, SV3.2
OUT6: R3.2, R4.2, SV3.3
OUT7: R1.2, R2.2, SV3.4
OUT8: R23.2, R24.2, SV3.5
OUT9: R21.2, R22.2, SV3.6
OUT14: R19.2, R20.2, SV3.7
OUT15: R17.2, R18.2, SV3.8
OUT16: R39.2, R40.2, SV3.9
OUT17: R37.2, R38.2, SV3.10
OUT22: R35.2, R36.2, SV3.11
OUT23: R33.2, R34.2, SV3.12
OUT24: R55.2, R56.2, SV3.13
OUT25: R53.2, R54.2, SV3.14
OUT30: R51.2, R52.2, SV3.15
OUT31: R49.2, R50.2, SV3.16
V+: J1.1, R65.2, SV3.17
V-: J1.3, R66.2, SV3.19

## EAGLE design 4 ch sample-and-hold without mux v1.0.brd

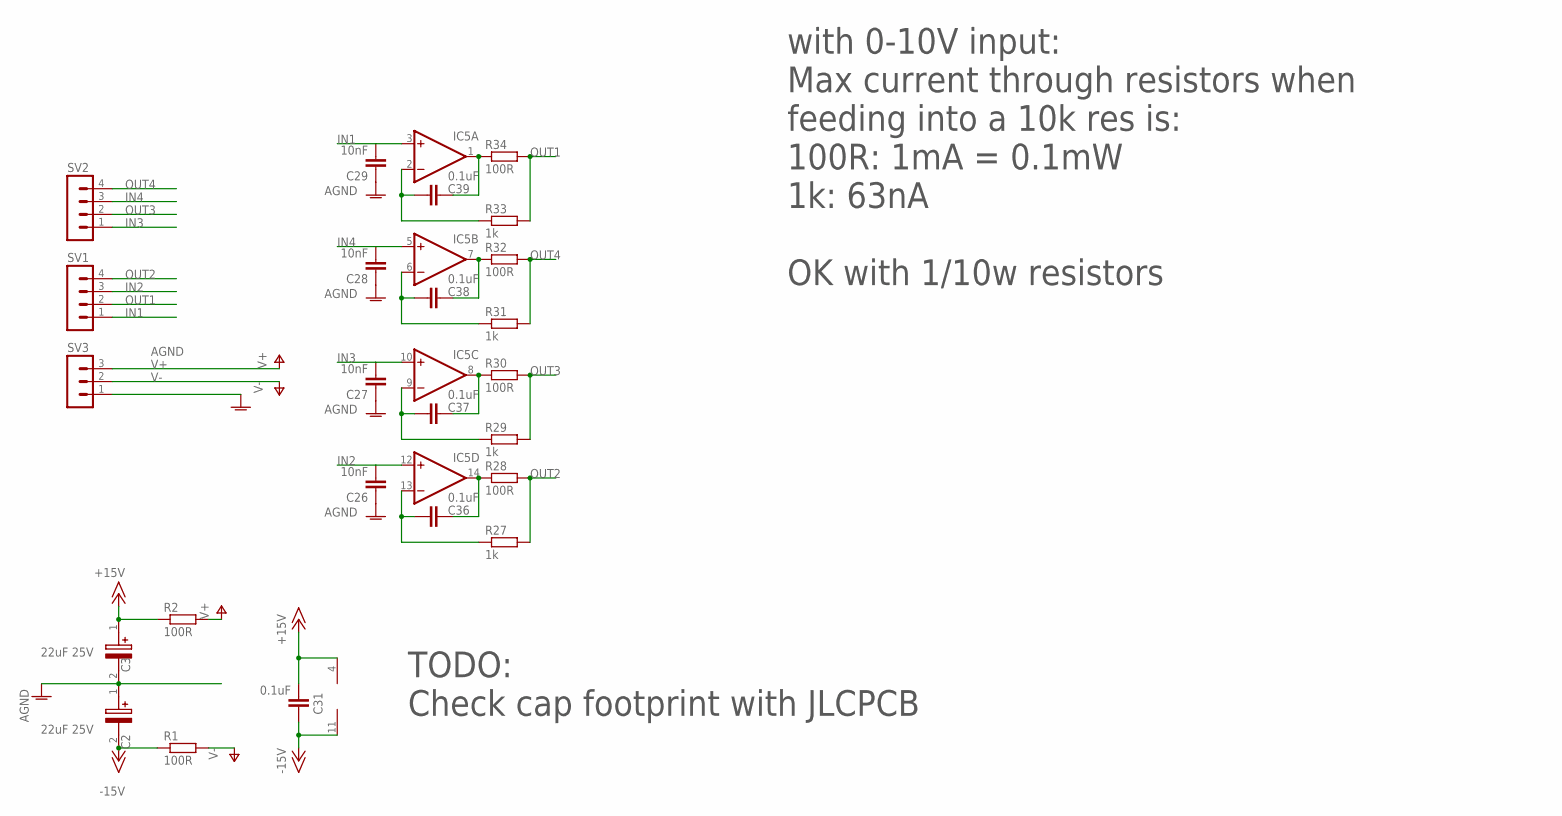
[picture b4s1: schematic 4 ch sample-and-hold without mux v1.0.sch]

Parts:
C2, C3: 22uF 25V; CAPAE660X610N
C26, C27, C28, C29: 10nF; C0805
C31, C36, C37, C38, C39: 0.1uF; C0603
IC5: TL074D; SO14
R1, R2: 100R; R0805
R27, R29, R31, R33: 1k; R0603
R28, R30, R32, R34: 100R; R0603
SV1, SV2: MA04-1JP; SIP-PIN04-1J
SV3: MA03-1JP; SIP-PIN03-1J

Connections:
+15V: C3.1 (+), C31.1, IC5.4 (V+), R2.1
-15V: C2.2 (-), C31.2, IC5.11 (V-), R1.1
AGND: C2.1 (+), C3.2 (-), C26.1, C27.1, C28.1, C29.1, SV3.1
IN1: C29.2, IC5.3 (+IN), SV1.1
IN2: C26.2, IC5.12 (+IN), SV1.3
IN3: C27.2, IC5.10 (+IN), SV2.1
IN4: C28.2, IC5.5 (+IN), SV2.3
unnamed: C39.1, IC5.1 (OUT), R34.1
unnamed: C39.2, IC5.2 (-IN), R33.1
unnamed: C38.1, IC5.7 (OUT), R32.1
unnamed: C38.2, IC5.6 (-IN), R31.1
unnamed: C37.1, IC5.8 (OUT), R30.1
unnamed: C36.1, IC5.14 (OUT), R28.1
unnamed: C37.2, IC5.9 (-IN), R29.1
unnamed: C36.2, IC5.13 (-IN), R27.1
OUT1: R33.2, R34.2, SV1.2
OUT2: R27.2, R28.2, SV1.4
OUT3: R29.2, R30.2, SV2.2
OUT4: R31.2, R32.2, SV2.4
V+: R2.2, SV3.3
V-: R1.2, SV3.2

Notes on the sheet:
TODO: Check cap footprint with JLCPCB
with 0-10V input: Max current through resistors when feeding into a 10k res is: 100R: 1mA = 0.1mW 1k: 63nA OK with 1/10w resistors
